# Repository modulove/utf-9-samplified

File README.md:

# UTF-9-samplified Drum Computer  

This project is based on the [bleep drum](https://bleeplabs.com/product/the-bleep-drum/) design by Dr. Bleep.

In 2025, **Felix Wiegeand (wgdmodular)** picked it up and released this **utf-9-samplified drum machine clone** with nice upgrades that make it perfect for starters and pros.

We (Modulove) put these into the hands of **beginners at DIY synthesizer solder workshops in 2025**.

- Few dozens were built.
- Every single one worked :)
- All were **hand-soldered by beginners (even kids!)**.

It turned out to be a **perfect entry-level project**.

The new firmware adds **Additonal functionality, fixes, and performance tricks** that came out of those builds and feedback from users.

---

## Firmware Updates

**Stable firmware (recommended):** 
Fixes the **button confusion issue**, fixed bad button behavior, small optimizations.
[https://dl.modulove.de/module/utf9/](https://dl.modulove.de/module/utf9/)

**Beta firmware (optional):**
Adds the new features: save/load slots, MIDI-to-CV clock, and more.
[https://dl.modulove.de/module/utf9/beta.html](https://dl.modulove.de/module/utf9/beta.html) 

Flash tool & instructions: [https://dl.modulove.de/module/utf9/](https://dl.modulove.de/module/utf9/)

---

## Supported boards

The firmware builds from a single sketch for three targets:

| Board | Notes |
|---|---|
| Arduino Nano | ATmega328P, new bootloader (115200 baud) |
| Arduino Nano (Old Bootloader) | ATmega328P, 57600 baud |
| LGT8F328P | Nano clone, built at `clock_div=2` so the chip runs at 16 MHz |

The LGT8F328P is an AVR-compatible clone whose internal RC oscillator runs at
32 MHz. The build divides it to 16 MHz so every timing in the sketch matches
the Nano, and the sample clock is derived from `F_CPU` rather than hardcoded,
so it lands on 9803.9 Hz on both. The LGT8F has no real EEPROM - the core
emulates it in flash, where writing one byte erases and rewrites a 1 KB page -
so pattern saves are staged and written as a single burst there.

None of this costs the Nano anything: the ATmega builds are byte-for-byte the
same size as before the dual-platform change.

**The Standard drumkit is Nano-only.** The LGT8F bootloader reserves 3 KB,
leaving 29696 bytes against the Nano's 30720, and Standard's sample set builds
to 30658. The other five kits all fit.

---

## Documentation

Docs of the **new features** here:

[docs/README.md](./docs/README.md)

The BOM is the docs/ folder as well.
[docs/BOM.md](./docs/BOM.md)

Find the ibom here:
[https://dl.modulove.de/module/utf9/ibom.html](https://dl.modulove.de/module/utf9/ibom.html)

---

## Links

The original Bleep Drum 
[https://bleeplabs.com/product/the-bleep-drum/](https://bleeplabs.com/product/the-bleep-drum/).

Old Bleep Drum User Guide & Hacking Info
[https://bleeplabs.com/bleep-drum-user-guide/](https://bleeplabs.com/bleep-drum-user-guide/).

---

## 💜 Thank You

Thanks for building with us
and huge thank yoouu to Felix from WGD Modular & John-Mike Reed aka Dr. Bleep who has been designing the initial Bleep Drum.

Linus & the Modulove workshop team

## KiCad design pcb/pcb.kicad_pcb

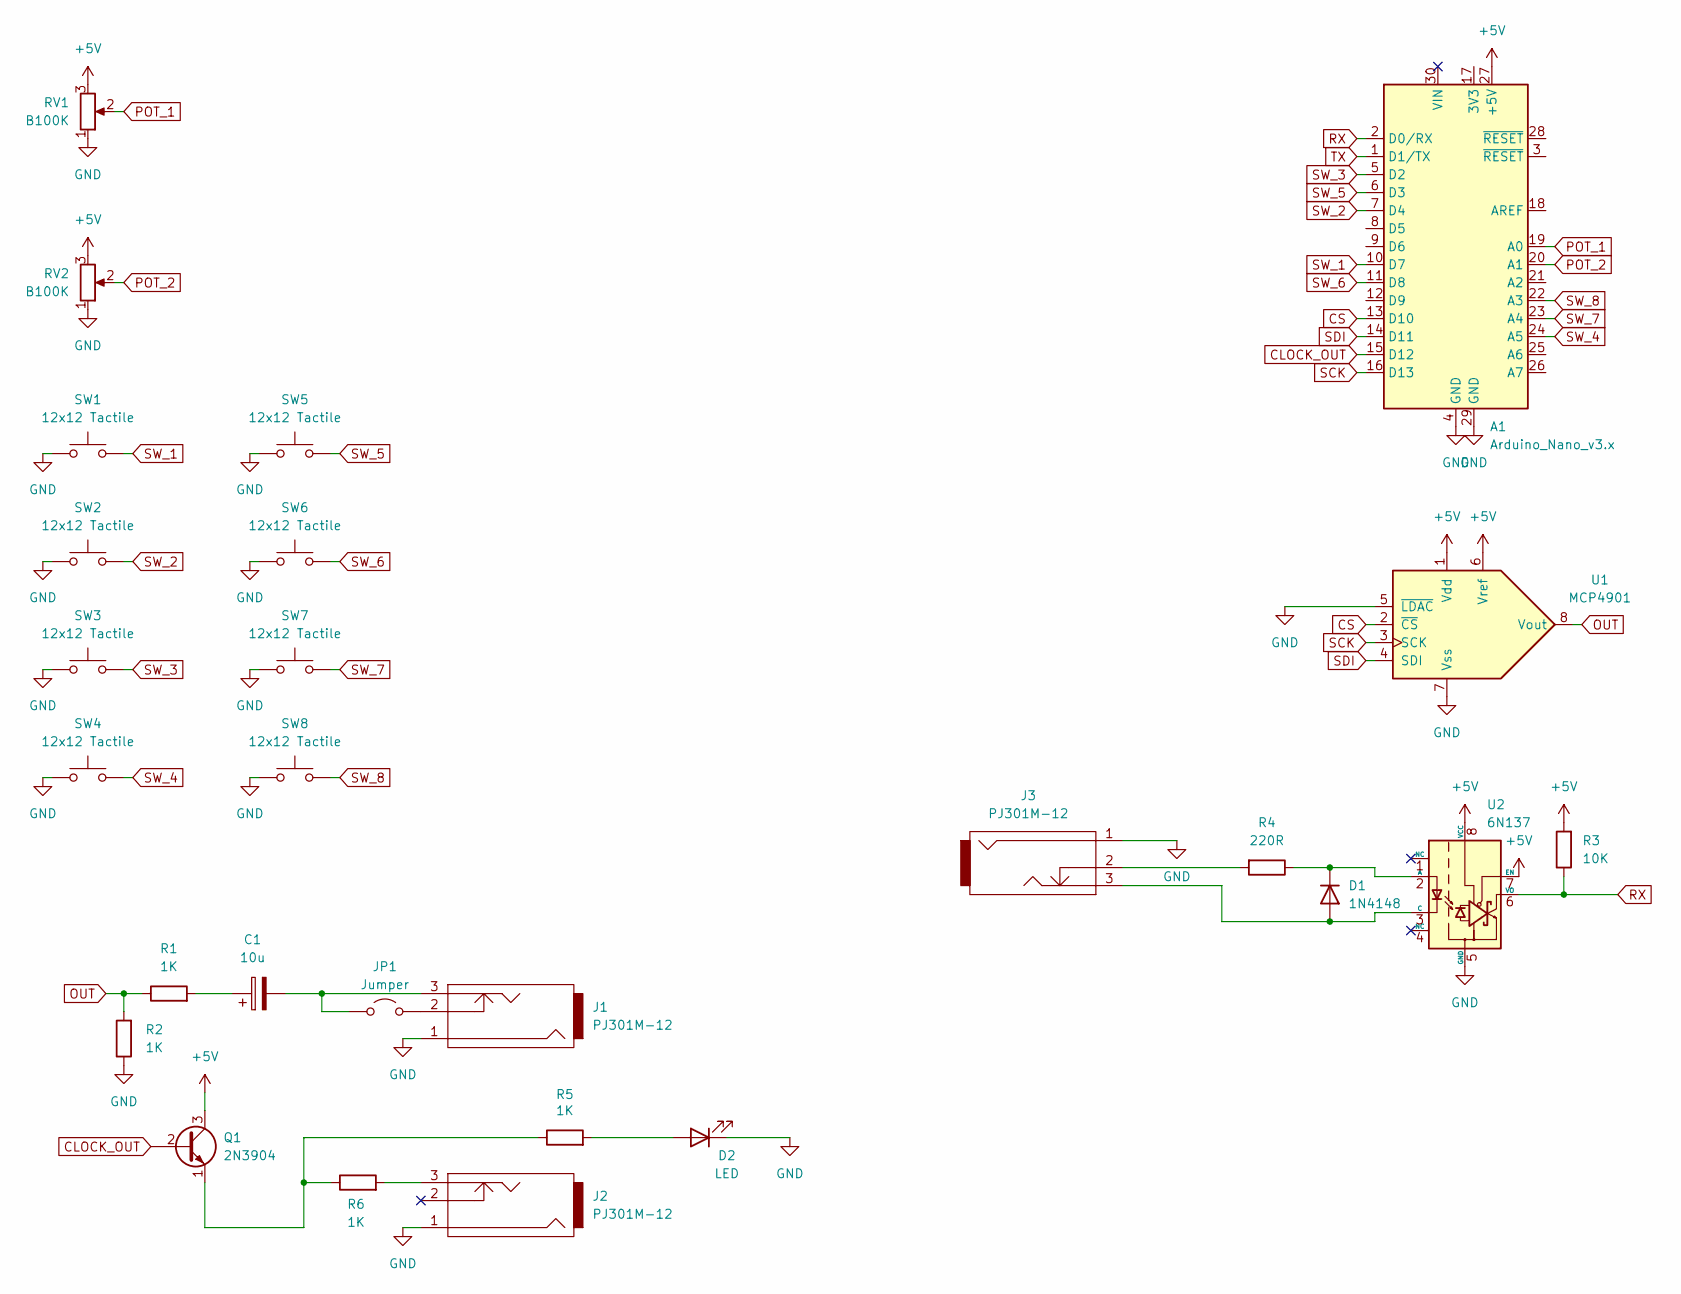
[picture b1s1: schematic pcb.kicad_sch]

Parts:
A1: Arduino_Nano_v3.x; Arduino_Nano
C1: 10u; CP_Radial_D5.0mm_P2.50mm
D1: 1N4148; D_DO-35_SOD27_P7.62mm_Horizontal
D2: LED; LED_D5.0mm
J1, J2, J3: PJ301M-12
JP1: Jumper; TestPoint_2Pads_Pitch2.54mm_Drill0.8mm
Q1: 2N3904; TO-92_Inline
R1, R2, R5, R6: 1K; R_Axial_DIN0207_L6.3mm_D2.5mm_P7.62mm_Horizontal
R3: 10K; R_Axial_DIN0207_L6.3mm_D2.5mm_P7.62mm_Horizontal
R4: 220R; R_Axial_DIN0207_L6.3mm_D2.5mm_P7.62mm_Horizontal
RV1, RV2: B100K; Potentiometer_Alpha_RD901F-40-00D_Single_Vertical
SW1, SW2, SW3, SW4, SW5, SW6, SW7, SW8: 12x12 Tactile; SW_PUSH-12mm
U1: MCP4901; DIP-8_W7.62mm
U2: 6N137; DIP-8_W7.62mm

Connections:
+5V: A1.27 (+5V), Q1.3 (C), R3.2, RV1.3, RV2.3, U1.1 (Vdd), U1.6 (Vref), U2.7 (EN), U2.8 (VCC)
CLOCK_OUT: A1.15 (D12), Q1.2 (B)
CS: A1.13 (D10), U1.2 (~CS)
GND: A1.4 (GND), A1.29 (GND), D2.1 (K), J1.1, J2.1, J3.1, R2.1, RV1.1, RV2.1, SW1.1, SW2.1, SW3.1, SW4.1, SW5.1, SW6.1, SW7.1, SW8.1, U1.5 (~LDAC), U1.7 (Vss), U2.5 (GND)
unnamed: C1.1, R1.2
unnamed: D1.2 (A), J3.3, U2.3 (C)
unnamed: D1.1 (K), R4.1, U2.2 (A)
unnamed: D2.2 (A), R5.2
unnamed: J2.3, R6.2
unnamed: J3.2, R4.2
unnamed: C1.2, J1.3, JP1.1 (A)
unnamed: J1.2, JP1.2 (B)
unnamed: Q1.1 (E), R5.1, R6.1
OUT: R1.1, R2.2, U1.8 (Vout)
POT_1: A1.19 (A0), RV1.2
POT_2: A1.20 (A1), RV2.2
RX: A1.2 (D0/RX), R3.1, U2.6 (VO)
SCK: A1.16 (D13), U1.3 (SCK)
SDI: A1.14 (D11), U1.4 (SDI)
SW_1: A1.10 (D7), SW1.2
SW_2: A1.7 (D4), SW2.2
SW_3: A1.5 (D2), SW3.2
SW_4: A1.24 (A5), SW4.2
SW_5: A1.6 (D3), SW5.2
SW_6: A1.11 (D8), SW6.2
SW_7: A1.23 (A4), SW7.2
SW_8: A1.22 (A3), SW8.2
TX: A1.1 (D1/TX)

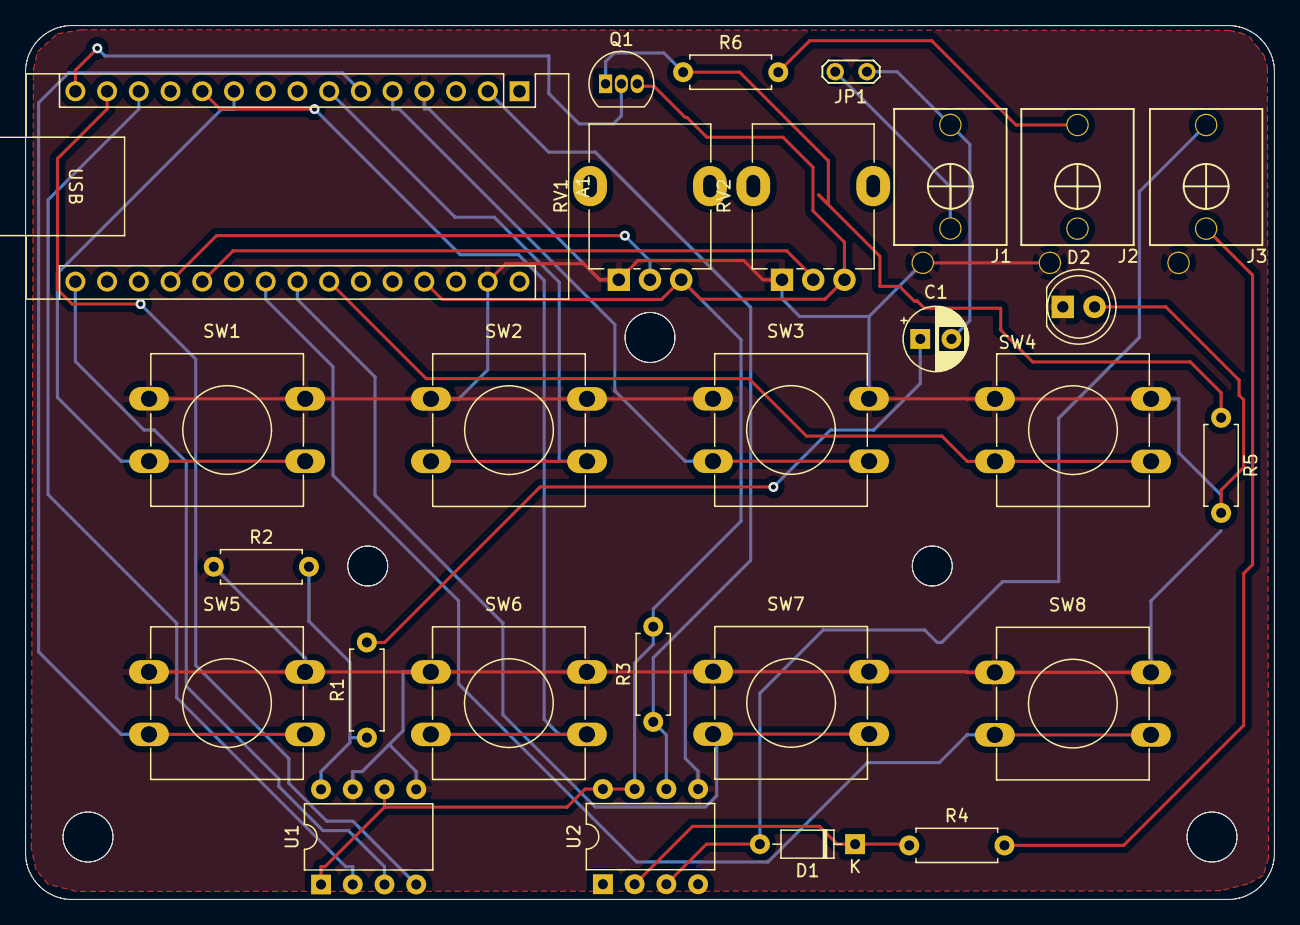
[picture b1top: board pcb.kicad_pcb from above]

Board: 2 copper layers, 100.0 x 70.0 mm, 27 parts (0 on the bottom side), 27 nets.

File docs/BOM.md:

### utf-9-samplified BOM


| Designator                      | Footprint                                         | Quantity  | Value             |
|---------------------------------|---------------------------------------------------|-----------|-------------------|
| SW1,SW4,SW2,SW6,SW5,SW8,SW7,SW3 | SW_PUSH-12mm                                      | 8         | 12x12 Tactile     |
| R2,R1,R6,R5                     | R_Axial_DIN0207_L6.3mm_D2.5mm_P7.62mm_Horizontal  | 4         | 1K                |
| R3                              | R_Axial_DIN0207_L6.3mm_D2.5mm_P7.62mm_Horizontal  | 1         | 10K               |
| J2                              | PJ301M-12                                         | 1         | PJ301M-12         |
| J3,J1                           | Stereo PJ301M-12                                  | 2         | Stereo PJ301M-12  |
| D2                              | LED_D5.0mm                                        | 1         | LED               |
| RV2,RV1                         | Potentiometer_Alpha_RD901F-40-00D_Single_Vertical | 2         | B100K             |
| U2                              | DIP-8_W7.62mm                                     | 1         | 6N137             |
| Q1                              | TO-92_Inline                                      | 1         | 2N3904            |
| D1                              | D_DO-35_SOD27_P7.62mm_Horizontal                  | 1         | 1N4148            |
| R4                              | R_Axial_DIN0207_L6.3mm_D2.5mm_P7.62mm_Horizontal  | 1         | 220R              |
| U1                              | DIP-8_W7.62mm                                     | 1         | MCP4901           |
| C1                              | CP_Radial_D5.0mm_P2.50mm                          | 1         | 10u               |
| JP1                             | TestPoint_2Pads_Pitch2.54mm_Drill0.8mm            | 1         | Jumper            |
| A1                              | Arduino_Nano                                      | 1         | Arduino_Nano_v3.x |

Make sure to flash the Arduino first and then solder it in directly - otherwise it will be too high and the frontpanel wont fit. Make sure you have a genuine arduino nano!

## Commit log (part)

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2024-10-20 Finish Rev 1
2024-12-23 Revert MIDI jack
2024-12-23 Fix clock output
2025-02-28 Add firmware
2025-03-08 Fix BOM
2025-08-18 Fix buttons in firmware.ino
    correct pull-ups, clean up a bit
2025-08-18 clean RGB led from firmware.ino
    No RGB Led in there
2025-08-19 Update with bugfix and new features
    This fixes a few oversights.
    Adds EEPROM save functionality.
    Midi Channel selection at boot is in again.
    Need some more testing still (MIDI anyone?)
2025-08-22 Create README.md
    Experimented with AI for documentation here..
2025-08-22 Update README.md
    remove bs flowcharts etc
2025-08-24 Update README.md
    less is more
2025-08-24 Update README.md
    fix
2025-08-25 Create BOM.md
    move BOM to docs/ folder
2025-08-25 Update README.md
    more soon
2025-08-25 Update README.md
    docs and update README
2025-08-25 Update README.md
    ibom & formatting
2025-08-25 Update README.md
    Add Links / resources
2025-08-25 Update README.md
    no bank switching for now
2025-08-26 Aktualisieren von README.md
2025-08-26 Aktualisieren von README.md
    More focus, less bloat
2025-10-28 Add UTF-9 latest version (default drumset)
2025-10-28 Add default drumset README file
2025-10-28 mv default drumkit
2025-10-28 add fw variants
2025-10-28 Fix MIDI library installation name
    Changed from 'MIDI' to 'MIDI Library' (the correct Arduino Library Manager name)
    This resolves the build error:
    Error installing MIDI: Library 'MIDI' not found
2025-10-28 Fix board FQBN for old bootloader compilation
    Changed from 'nanoOldBootloader' to 'nano:cpu=atmega328old' which is the correct
    Arduino board variant identifier.
    Correct FQBNs:
    - New bootloader: arduino:avr:nano
    - Old bootloader: arduino:avr:nano:cpu=atmega328old
    This resolves the build error:
